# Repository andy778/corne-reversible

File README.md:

# corne-reversible

A wireless Corne-layout split keyboard built on one reversible PCB: the same board is used face-up for the left half and flipped for the right, so a single JLCPCB order of 5 boards covers two keyboards and a spare.

- 3x6+3 (42 keys), with a break-off outer column for 36 keys
- Hot-swap sockets for Kailh MX or Kailh Choc on the same footprint
- Pro Micro-footprint nRF52840 controller (nice!nano v2 or clone), ZMK firmware
- JLCPCB fits the diodes and the reset button (both Basic parts); everything else is hand-soldered
- 3D printed case and plate

Status: planning. Nothing has been fabricated or tested yet.

## Documents

- [Design and build plan](docs/plan.md)
- [Work packages](docs/work-packages.md)

## Layout

| Folder | Contents |
| --- | --- |
| `docs/` | Plan, work packages, build notes |
| `pcb/` | Ergogen config, KiCad project, fabrication outputs |
| `firmware/` | ZMK config and keymap |
| `case/` | Parametric case and plate sources, printable files |

## Licence

Hardware and software in this repository are released under the [MIT Licence](LICENSE). Copyright (c) 2026 andy778.

Third-party footprints and other imported design files keep their own licences. Each one is recorded in `pcb/footprints/THIRD_PARTY.md`.

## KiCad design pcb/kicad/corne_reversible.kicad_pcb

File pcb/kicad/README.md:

# KiCad board (WP7)

Routed KiCad 10 project for one reversible Corne half. LEFT half = KiCad F side up, RIGHT half = the same board flipped (KiCad B up). JLCPCB assembles KiCad B (face A): 21 diodes and the reset button. Fabrication outputs are in [`../fab/`](../fab/README.md).

**Status:** routed, KiCad DRC 0 errors, geometric netlist check passing for both halves. **Not reviewed:** WP8 does the independent pre-order review. Nothing here has been sent to JLCPCB.

## Contents

| Path | What |
| --- | --- |
| `corne_reversible.kicad_pcb` / `.kicad_pro` | The board and its design rules (generated, do not hand-edit without re-running the checks) |
| `fp-lib-table` | Project libraries: `corne_reversible` = `../footprints/corne_reversible.pretty` (WP5), `corne_kicad_local` = `corne_kicad_local.pretty` |
| `corne_kicad_local.pretty/` | The two Ergogen-local footprints (SOD-123 diode on face A, M2 hole), exported in front form so KiCad can check board copies against them |
| `tools/build_board.py` | Builds the routed board from the Ergogen output (see Regenerate) |
| `tools/router.py` | The small grid maze router `build_board.py` uses for the inter-key nets |
| `tools/check_netlist.py` | Electrical check from copper geometry, both halves; output in `netlist-check.txt` |
| `tools/make_fab.py` | Gerbers, drill, JLCPCB BOM/CPL, previews into `../fab/` |
| `tools/kutil.py` | pcbnew helpers |
| `drc-report.txt` | `kicad-cli pcb drc --severity-all` of the committed board |
| `netlist-check.txt` | Output of `check_netlist.py` on the committed board |

## Regenerate

Tools used: Ergogen **4.2.1** (`npx`), KiCad **10.0.6** (`kicad-cli`, and the `pcbnew` Python module of the system Python, `/usr/bin/python3`, 3.14 on the build machine), `shapely` 2.1, `numpy`, `scipy`, `Pillow`. Freerouting was not installed and not used.

```sh
cd pcb/ergogen && npx -y ergogen@4.2.1 . -o output --clean --debug --svg && python3 check.py && cd ../..
/usr/bin/python3 pcb/kicad/tools/build_board.py          # about 5 minutes; deterministic
(cd pcb/kicad && kicad-cli pcb drc --severity-all -o drc-report.txt corne_reversible.kicad_pcb)
/usr/bin/python3 pcb/kicad/tools/check_netlist.py > pcb/kicad/netlist-check.txt
/usr/bin/python3 pcb/kicad/tools/make_fab.py
```

`build_board.py` reads `pcb/ergogen/output/pcbs/corne_reversible.kicad_pcb` (KiCad 5 format from Ergogen), and:

1. assigns the JLCPCB data (value, `LCSC` field) to the diodes (C81598) and the TS-1187A (C318884), and points the two Ergogen-local footprints at `corne_kicad_local`;
2. removes the net from the placeholder battery jumper pads (`BAT+`/`BAT-`) and from the power switch's unused pin 3 (see Power);
3. places a fixed per-key template (identical for all 21 keys, rotated with the key): it joins the four column socket pads, the four anode socket pads and the diode anode, and puts a via on the diode cathode;
4. places the controller fan-out stubs (see Controller) and the nice!view jumper stubs and lanes;
5. routes everything else with `router.py` (0.05 mm grid, two layers, then pulled straight with exact clearance checks), in a fixed order with per-net layer preferences: power and display nets first on the right of the controller, then rows (F preferred) and columns (B preferred) inside the key field, then the long column and row runs into the controller;
6. removes router leftovers (dead-end stubs, single-layer vias) and trims overhangs at T-junctions;
7. moves the controller's jumper instruction text clear of the nice!view labels and adds the version and half labels.

## Board

| | |
| --- | --- |
| Size | **146.28 x 84.01 mm** (outline bounding box, 42-key), 100.9 cm2. 2 layers, 1.6 mm |
| Origin | KiCad (0, 0) = centre of the outer-column bottom key; Ergogen coordinates are the same with y negated |
| Copper | 669 track segments (3.15 m), 106 vias (0.6/0.3 mm) |
| Mounting holes | M2, 2.2 mm NPTH, Ergogen frame: H1 (30.075, 32.65), H2 (65.675, 34.54), H3 (30.075, 13.6), H4 (85.725, -25.645), H5 (115.75, 3.855). H1-H4 moved in this WP for the case inserts (see `pcb/ergogen/README.md`) |
| Break line | x = 9.525 (KiCad), 38 NPTH holes of 0.6 mm (footprint `BRK1`, converted from Ergogen's Edge.Cuts circles by `build_board.py`, WP8 S1) |

## Design rules (JLCPCB 2-layer, from docs/bom.md)

Conservative values where space allows; the absolute JLCPCB minimum is in brackets.

| Rule | Board setting | JLCPCB |
| --- | --- | --- |
| Clearance, copper to copper | 0.20 mm | 0.10 (0.15 recommended) |
| Track width, minimum | 0.20 mm (only the nice!view lanes use 0.20) | 0.10 |
| Signal tracks | 0.25 mm | |
| Power tracks | BAT_P 0.50, RAW 0.50, GND 0.40 (JST, reset, controller), VCC 0.30 mm; 0.30 mm where they pass between the controller hole rows (0.84 mm gaps). nice!view GND 0.25 | |
| Vias | 0.6 mm pad / 0.3 mm drill (ring 0.15) | 0.15 / 0.25 min, 0.2 hole preferred |
| Minimum via annular ring | 0.15 mm (the controller's 0.7/0.3 via-pads have 0.20) | |
| Minimum through hole | 0.30 mm | 0.15 (via), 0.2 preferred |
| Copper to drill hole | 0.25 mm | |
| Hole to hole | 0.50 mm | 0.20 via, 0.45 pad |
| Copper to board edge (incl. mouse-bite holes) | 0.30 mm | 0.20 |
| Text height / thickness | 0.8 / 0.15 mm (footprint silk is 0.9 mm) | 1.0 mm recommended, 0.15 line |

Net classes: Default 0.25, Power (BAT_P, RAW) 0.5, Ground (GND) 0.4, Logic3V3 (VCC) 0.3, all 0.2 mm clearance.

## Routing decisions

**Per key** (template, key frame; B = KiCad B.Cu, F = KiCad F.Cu): column pads 1 are on B on the right of the key and on F on the left; anode pads 2 the other way round. Column: F Choc - F MX, an F track over the top of the key to a via, B to the B Choc pad, B Choc - B MX. Anode: B Choc - B MX down the left side, F Choc - F MX down the right side, both into a via below the MX pads, B to the diode anode. Row: diode cathode on B to a via left of the diode. Column trunks run vertically on B, rows horizontally on F, so the key field is close to a Manhattan grid.

**Matrix to controller.** The long column runs (the outer columns in particular) go along the top edge of the key field or through the gaps between key rows, then down the strip left of the controller; rows enter the same strip from the key field and the thumb cluster. The router chose these paths; see the previews. Thumb keys connect to their column nets (near = D18 under the index column, mid = D15, far = D14).

**Controller** (`MCU1`, socketed, face-up on both halves). The board net goes to the centre via-pad of each pin exactly as `pcb/footprints/README.md` describes; the jumpers select the half. Each used via-pad is reached by a hand-placed stub through the gap between two hole rows (0.84 mm between hole pads), on the face and side where the via-pad has no link of another net. Left side: columns on F (D21 ... D14), rows on B (D4 ... D7). Right side: RAW, GND, RST, VCC on B; D1 (CS), D2 (MOSI), D3 (SCK) on F. The three controller GND via-pads are tied inside the footprint: the adjacent pair of rows 2/3 with a short B track, rows 3/4 through their two F-side GND jumper pads (both are GND-side pads, so this is plain GND copper on both halves). Nothing else is routed between the hole columns.

**nice!view.** Each jumper target pad gets a stub out of its mask aperture, away from the jumper gap. F pads dog-leg to a via 0.9 mm to their left; B pads go straight down. Under the header four nested lanes per face (0.20 mm) run to the right, where the router joins them to the controller. CS = D1, MOSI = D2, SCK = D3, plus VCC and GND, both halves (checked).

**Power.** JST pin 2 (BAT_P, both hole pairs) -> MSK12C02 pin 1 (both faces) ; MSK12C02 common pin 2 (both faces) -> controller RAW. JST pin 1 and the reset button go to GND. Decision on the WP5 battery placeholder holes `HB1`/`HB2` (B+/B-): **kept, but their jumper target pads have no net and nothing is routed to them.** The plan asked for the holes, and on a socketed nice!nano or SuperMini the battery reaches the controller through RAW. With no copper on the target pads, bridging a B+/B- jumper on either or both faces connects the hole to an isolated pad, so the CRITICAL battery short in the WP5 hazard table cannot happen on this board. If a future controller needs B+ there, that is a board change.

**Mounting holes.** The router keeps its copper at least 2.6 mm (copper edge) from every mounting-hole centre, outside an M2 screw head (3.8 mm). Measured nearest copper edge from the centre: H1 2.60, H2 2.35, H3 2.60, H4 2.61, H5 1.50 mm. H5's 1.50 mm is the nice!view MOSI lane on F (and the CS lane on B, under the plastic boss); a single net under the screw head cannot short to anything even if the mask is scratched, but a nylon washer at H5 costs nothing.

**Reset.** TS-1187A pin 1 (both pads) -> RST, pin 2 (both pads) -> GND.

**Break-off tab.** Only COL_D21, ROW0, ROW1 and ROW2 cross x = 9.525 (checked); they cross in the three gaps of the perforation, at least 0.30 mm from every bite hole. No other copper is in the tab. With the tab removed the remaining 18 keys and everything else stay connected (checked).

**No ground pour.** GND only has to connect the JST, the reset button, three controller via-pads and the display, all within 30 mm of each other on the right of the controller; tracks do that. A pour on both faces would sit against the hand-bridged jumper pads (a solder blob could reach it), wick heat from the socket pads, need a keep-out along the break line, and put copper under the controller module's antenna end. So none.

**Silkscreen.** From WP5: `LEFT HALF: BRIDGE 24 PIN / JUMPERS ON THIS FACE ONLY / USB / CONTROLLER FACE UP` on F and the `RIGHT HALF` version on B (moved below the nice!view header so it no longer overlaps the display pin labels), pin names at every controller hole and nice!view hole on both faces, `LEFT: bridge 4` / `RIGHT: bridge 4` at the display, B+/B- marked. Added: `corne-reversible v1.0 2026-11-15` on both faces and `LEFT HALF: THIS FACE UP` (F) / `RIGHT HALF: THIS FACE UP` (B). Polarity: every diode has a cathode bar on B silk at the cathode pad; the JST has `+`/`-` and `USE THIS PAIR` on F; on B (next to the controller pin labels) only `+`/`-`, set beside the B pair in the gaps between the labels; the F pair has no B silk, so the marked pair is the one to use (WP8 S2).

## DRC result

`drc-report.txt`, KiCad 10.0.6, all severities: **0 errors, 0 unconnected items, 69 warnings**, none excluded. Accepted warnings:

| Count | Type | Why accepted |
| --- | --- | --- |
| 42 | `hole_to_hole` | The two overlapping 3.0 mm MX socket holes per key (2 per key), inherent to the reversible MX footprint (WP5). The fab drills a figure-8; JLCPCB's DFM may ask, answer "intended". Left as warnings rather than DRC exclusions so they stay visible on every run |
| 16 | `npth_inside_courtyard` | The break-line NPTH holes (`BRK1`) sit on the key-tile boundary, inside the socket courtyards; copper is at least 0.30 mm away. The same holes were outline circles before WP8 S1 and drew no finding then |
| 8 | `silk_over_copper` | Controller pin labels next to the JST/reset pads; JLCPCB clips silk on pads. Legibility of a few right-half pin labels (B face, D2-D8) is reduced; the pin map is printed on the F face and in the WP5 README |
| 2 | `silk_overlap` | The same labels touching the reset and JST outlines |
| 1 | `lib_footprint_mismatch` | `SW22` (TS-1187A): value and the `LCSC` field were set on the board copy |

All other footprints match their library copies, which also confirms that the Ergogen modules and the WP5 `.kicad_mod` files are the same footprints.

## Netlist check

`tools/check_netlist.py` builds connectivity from the copper itself (pads, tracks, vias, plated holes), bridges the jumpers of one face (LEFT: F, RIGHT: B), maps each controller hole to the Pro Micro pin that lands in it on that half (mirrored on the right half) and asserts per key: column pin -> all four pad-1 socket pads, pad 2 -> diode anode, diode cathode -> row pin, for both halves against the stock ZMK Corne pin map; power, reset and nice!view wiring; no two controller pins sharing copper; unused pins isolated; the 36-key break; the break-line crossings; that bridging both faces does short pins (the documented hazard); and that every copper island carries one net name. Result on the committed board: `netlist-check.txt`, **271 checks, ALL PASS**.

## Known limits

- The router is mine and simple; routes are valid (DRC) but not pretty in places, notably around the nice!view and on the right of the controller. Open the board in KiCad before ordering.
- The right edge layout (power switch, reset, JST next to the controller) is WP4's and is tight; see the silk warnings above.
- Everything listed under "Unverified" in `pcb/footprints/README.md` and `pcb/ergogen/README.md` still applies.

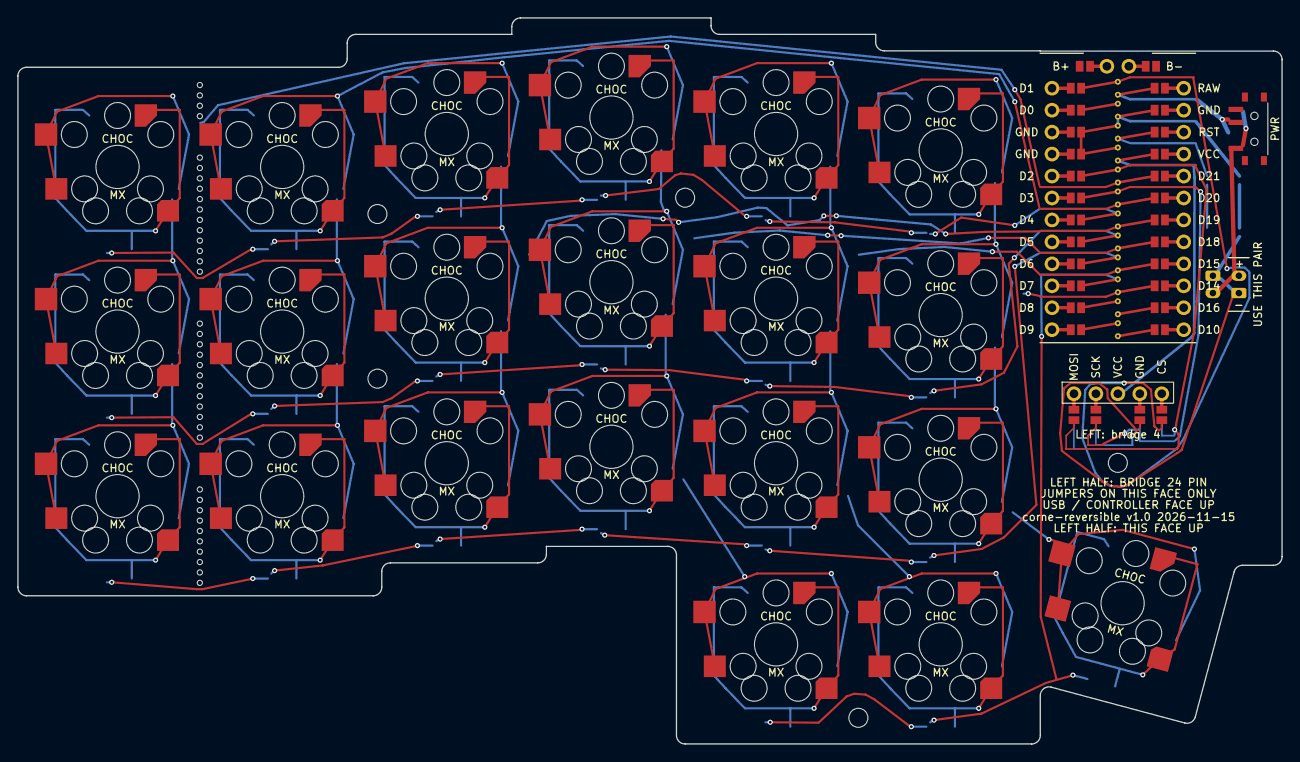
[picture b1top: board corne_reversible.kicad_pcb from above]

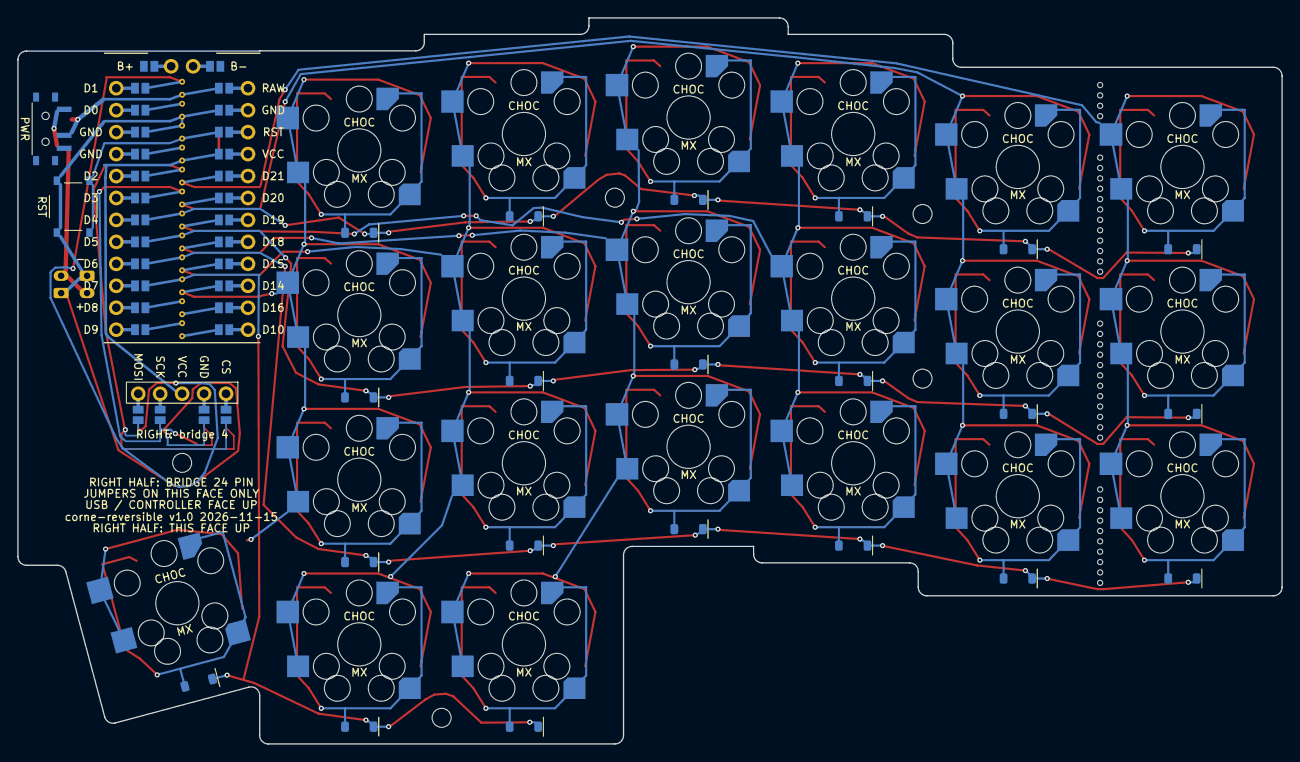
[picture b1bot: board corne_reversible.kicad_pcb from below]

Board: 2 copper layers, 146.3 x 84.0 mm, 53 parts (22 on the bottom side), 39 nets.

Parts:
BRK1: BreakLine_Perforation_NPTH
BT1: JST_PH_S2B-PH-K_Reversible
D1, D2, D3, D4, D5, D6, D7, D8, D9, D10, D11, D12, D13, D14, D15, D16, D17, D18, D19, D20, D21: 1N4148W; D_SOD-123_Back
DISP1: Display_niceview_Header_Reversible_Jumpers
H1, H2, H3, H4, H5: MountingHole_2.2mm_M2
MCU1: MCU_ProMicro_nRF52840_Reversible_Jumpers
PWR1: SW_SPDT_MSK12C02_Reversible
SW1, SW2, SW3, SW4, SW5, SW6, SW7, SW8, SW9, SW10, SW11, SW12, SW13, SW14, SW15, SW16, SW17, SW18, SW19, SW20, SW21: SW_MX_Choc_Hotswap_Reversible
SW22: TS-1187A-B-A-B; SW_Reset_TS-1187A_FaceA

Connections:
BAT_P: BT1.2, PWR1.1
COL_D14: MCU1.D14, SW16.1, SW17.1, SW18.1, SW21.1
COL_D15: MCU1.D15, SW13.1, SW14.1, SW15.1, SW20.1
COL_D18: MCU1.D18, SW10.1, SW11.1, SW12.1, SW19.1
COL_D19: MCU1.D19, SW7.1, SW8.1, SW9.1
COL_D20: MCU1.D20, SW4.1, SW5.1, SW6.1
COL_D21: MCU1.D21, SW1.1, SW2.1, SW3.1
DISP_CS: DISP1.CS, MCU1.D1
DISP_MOSI: DISP1.MOSI, MCU1.D2
DISP_SCK: DISP1.SCK, MCU1.D3
GND: BT1.1, DISP1.GND, MCU1.GND, SW22.2
RAW: MCU1.RAW, PWR1.2
ROW0: D3.1, D6.1, D9.1, D12.1, D15.1, D18.1, MCU1.D4
ROW1: D2.1, D5.1, D8.1, D11.1, D14.1, D17.1, MCU1.D5
ROW2: D1.1, D4.1, D7.1, D10.1, D13.1, D16.1, MCU1.D6
ROW3: D19.1, D20.1, D21.1, MCU1.D7
RST: MCU1.RST, SW22.1
SW_far_thumb: D21.2, SW21.2
SW_index_bottom: D13.2, SW13.2
SW_index_home: D14.2, SW14.2
SW_index_top: D15.2, SW15.2
SW_inner_bottom: D16.2, SW16.2
SW_inner_home: D17.2, SW17.2
SW_inner_top: D18.2, SW18.2
SW_mid_thumb: D20.2, SW20.2
SW_middle_bottom: D10.2, SW10.2
SW_middle_home: D11.2, SW11.2
SW_middle_top: D12.2, SW12.2
SW_near_thumb: D19.2, SW19.2
SW_outer_bottom: D1.2, SW1.2
SW_outer_home: D2.2, SW2.2
SW_outer_top: D3.2, SW3.2
SW_pinky_bottom: D4.2, SW4.2
SW_pinky_home: D5.2, SW5.2
SW_pinky_top: D6.2, SW6.2
SW_ring_bottom: D7.2, SW7.2
SW_ring_home: D8.2, SW8.2
SW_ring_top: D9.2, SW9.2
VCC: DISP1.VCC, MCU1.VCC

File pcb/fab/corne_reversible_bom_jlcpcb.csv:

Comment,Designator,Footprint,LCSC Part #
1N4148W,"D1,D2,D3,D4,D5,D6,D7,D8,D9,D10,D11,D12,D13,D14,D15,D16,D17,D18,D19,D20,D21",D_SOD-123_Back,C81598
TS-1187A-B-A-B,SW22,SW_Reset_TS-1187A_FaceA,C318884

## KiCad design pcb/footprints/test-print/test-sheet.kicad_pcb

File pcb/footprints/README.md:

# Footprints (WP5)

Reversible footprints for the corne-reversible board, in KiCad and Ergogen form, plus the checks and the 1:1 paper test sheet.

**Status:** generated, KiCad DRC-checked and geometry-checked. **Paper-tested:** the WP5 acceptance check, a 1:1 test fit with real parts (see [Paper test](#paper-test)), passed on 2026-11-15.

## Contents

| Path | What |
| --- | --- |
| `corne_reversible.pretty/` | KiCad 8/9/10 footprint library (file format 20240108, opens in KiCad 8 and later) |
| `ergogen/` | Ergogen v4 footprint modules with the same geometry. Copy or symlink into `<ergogen project>/footprints/corne/` and use `what: corne/<file name>` |
| `tools/gen_footprints.py` | **Source of truth.** Generates both of the above. Edit this, never the outputs |
| `tools/check_footprints.py` | Geometry and clearance checker against JLCPCB 2-layer rules (needs `shapely`) |
| `tools/make_test_sheet.py` | Builds `test-print/test-sheet.kicad_pcb` and plots the PDF; also runs KiCad DRC |
| `test-print/test-sheet.pdf` | 1:1 printable sheet. Page 1 shows the KiCad F side; page 2 shows the KiCad B side seen from B |
| `test-print/drc-report.txt` | KiCad 10 DRC of the test board against JLCPCB rules |
| `THIRD_PARTY.md` | Sources, commits and licences |

Regenerate everything:

```sh
python3 pcb/footprints/tools/gen_footprints.py
python3 pcb/footprints/tools/check_footprints.py
python3 pcb/footprints/tools/make_test_sheet.py --pdf --drc
```

## Face convention (read this first)

The plan calls the faces A and B: face A is the underside of the left half and the top of the right half. Diodes go on face A.

The footprints assume this mapping:

| | LEFT half | RIGHT half |
| --- | --- | --- |
| Board orientation | KiCad **F** side up | flipped left to right, KiCad **B** side up |
| Face A (JLCPCB diodes) | underside = KiCad **B** | top = KiCad **B** |
| Sockets, power switch, reset, JST | soldered on KiCad B | soldered on KiCad F |
| Controller and nice!view | on top (KiCad F), component side up | on top (KiCad B), component side up |
| Jumpers to bridge | the ones on **KiCad F** (silk: `LEFT HALF: BRIDGE 24 PIN JUMPERS ON THIS FACE ONLY`) | the ones on **KiCad B** (silk: `RIGHT HALF: …`) |

So **WP7 places the diodes on KiCad B.Cu**, and JLCPCB assembles the bottom side. To use the opposite mapping, set `LEFT_FACE = "B"` in `gen_footprints.py` and regenerate. Every LEFT/RIGHT label and jumper net then swaps sides.

The flip is a left-right mirror: a point at KiCad (x, y) is seen at (-x, y) from the top of the right half. The USB end stays at -y on both halves.

## Footprints

All footprints are marked `exclude_from_pos_files exclude_from_bom` because only the diodes are factory-placed. WP7 can change that if a full BOM is wanted. **No hand-soldered pad has paste.** This matters most for the jumpers: paste on face-A jumpers would let JLCPCB's stencil bridge all of them. Do not add paste.

### `SW_MX_Choc_Hotswap_Reversible` / `ergogen/switch_mx_choc_reversible.js`

One key, 19.05 mm pitch. Origin is the key centre.

- **MX** (Kailh CPG151101S11) pads and holes are on the +y half. The MX switch is rotated 180 degrees (south-facing), which is what makes room for Choc. The socket pads are on both faces. The inner pad is chamfered to clear the other face's socket hole.
- **Choc** (Kailh CPG135001S30) pads and holes are on the -y half, on both faces, sharing the pin-1 hole at (0, -5.95). The inner pad is chamfered (50 %) to clear the other face's side hole.
- Centre hole is 5.0 mm, for the Choc V2 post. Each side peg uses one oval slot, 2.32 x 1.9 mm centred at ±5.29, which takes both the MX PCB-mount pegs (±5.08) and the Choc V1 pegs (±5.5).
- Pads: `1` = column side (`from`), `2` = diode side (`to`). Each net appears on 4 pads: MX F, MX B, Choc F, Choc B. The faces are **not joined inside the footprint**, so WP7 routes both. A switch is a plain contact, so the pad-to-net choice per socket is free; it was picked so pad 1 is at the outer x edge (column traces run vertically) and pad 2 is nearest the diode below for MX.
- Fab and courtyard layers: approximate socket outlines on both faces. Dwgs.User: 14 x 14 mm switch outline and 18.05 mm keycap outline.

### `MCU_ProMicro_nRF52840_Reversible_Jumpers` / `ergogen/mcu_promicro_reversible_jumpers.js`

Pro Micro footprint for the nice!nano v2 or a SuperMini. It is socketed and mounted **component side up on both halves**, with USB towards -y. The rows are 15.24 mm apart; holes are 1.0 mm drill with 1.7 mm pads, for machine-pin sockets.

- **Holes `H1`..`H24`** use Pro Micro numbering in the LEFT-half view: H1 is top-left (D1) and the numbering runs counter-clockwise. Each hole is a local net with nothing attached except its two jumpers.
- **Per hole, one jumper on each face** (0.9 x 1.25 mm pads, 0.3 mm gap, one shared mask opening, tented copper link to the hole):
  - KiCad F jumper: connects the hole to the pin the LEFT half seats there.
  - KiCad B jumper: connects the hole to the pin the RIGHT half seats there, which is the pin at the mirrored hole.
- **Signal pads** are named after the controller pin: `D0`..`D21`, `RAW`, `GND`, `RST`, `VCC`. Each signal has a 0.7 / 0.3 mm tented via-pad in the centre column (x = 0, y = row ± 0.75). Its F jumper and its mirrored B jumper are already tied to it inside the footprint. **WP7 routes the board net to that via.** In Ergogen, pass the board net as the param, e.g. `D4: ROW0`.
- **`BAT+` / `BAT-` (holes `HB1`, `HB2`)** sit next to the USB end at y = -15.24, x = ±1.27, with jumpers as for the other pins. They are a **placeholder**: see the unverified list. With a nice!nano v2 the normal battery path is JST, then power switch, then the `RAW` pin. Leave these unbridged and unrouted unless your controller really has B+/B- holes at exactly these positions.
- Silk on each face gives the pin name at every hole as seen on that half, plus the bridging instruction.
- The nice!nano extra pins (P1.01, P1.02, P1.07) are **not** included. They sit in different places on the nice!nano and the SuperMini, and the Corne does not need them.

### `Display_niceview_Header_Reversible_Jumpers` / `ergogen/display_niceview_reversible_jumpers.js`

A 5-pin 2.54 mm header. Seen from the top of the LEFT half, x = -5.08 to +5.08: **MOSI, SCK, VCC, GND, CS**. VCC is the centre pin and mirrors onto itself, so it is a plain pad `VCC`. The other four holes (`H1`, `H2`, `H4`, `H5`) each have one jumper per face, placed below the header:

| Hole (left view) | KiCad F jumper (LEFT) | KiCad B jumper (RIGHT) |
| --- | --- | --- |
| H1 (x = -5.08) | MOSI | CS |
| H2 (x = -2.54) | SCK | GND |
| H3 (x = 0) | VCC (no jumper) | VCC |
| H4 (x = +2.54) | GND | SCK |
| H5 (x = +5.08) | CS | MOSI |

The jumper target pads are named `MOSI`, `SCK`, `GND`, `CS`. They are **not** joined inside the footprint, because the F and B copies cross each other. WP7 routes them: MOSI to D2, SCK to D3, CS to D1, plus GND and VCC.

### Edge parts (soldered by hand on whichever face is the underside)

These parts carry their own pads on each face, mirrored, with the same pad numbers. So the pin function is right on both faces **without jumpers**. The F and B copies are separate copper that WP7 joins.

| Footprint | Part (WP3, LCSC, checked 2026-11-15) | Pads / nets | Notes |
| --- | --- | --- | --- |
| `SW_SPDT_MSK12C02_Reversible` | Shou Han MSK12C02, C431540 | `1` = BAT_P (from JST), `2` = common, goes to RAW, `3` = NC; 4 unnamed shell tabs; 2 NPTH | Actuator towards +y (board edge). Signal pads lengthened 0.4 mm away from the body for hand soldering. Because the B copy is mirrored, ON is the opposite slide direction on the two halves. |
| `SW_Reset_TS-1186F_Side_Reversible` | XKB TS-1186F-B-A, C908470. **Fallback only**: the owner chose the factory-fitted TS-1187A (below) | `1` = RST (pins 1+2), `2` = GND (pins 3+4); two 0.8 mm peg holes | Land pattern read from the XKB TS-1186F-X-X drawing; pads lengthened 0.4 mm outward. Actuator assumed towards +y. |
| `JST_PH_S2B-PH-K_Reversible` | JST S2B-PH-K-S, C173752, THT side entry | `1` = BAT_N (GND), `2` = BAT_P | THT holes are shared by both faces, so a connector fitted on the other face would swap polarity. This footprint therefore has **two hole pairs**: y = 0 for a connector on KiCad F, y = -3.0 for one on KiCad B, wired as mirror images. No jumpers, so there is no double-bridge battery short. Silk on each face marks `USE THIS PAIR`. Courtyard includes the plug and lead. |

### `SW_Reset_TS-1187A_FaceA` / `ergogen/reset_switch_ts1187a_face_a.js` (JLCPCB-assembled)

- XKB TS-1187A-B-A-B, C318884, **JLCPCB Basic** (no feeder fee): the owner chose to have JLCPCB fit it with the diodes, on face A only.
- Pads, paste and courtyard are KiCad's stock `SW_Push_1P1T_XKB_TS-1187A` (1.0 x 0.75 mm at x +-3.0, y +-1.875). `1` = RST, `2` = GND. Included in BOM and position files, unlike the hand-soldered footprints.
- The KiCad library copy is front-side; flip it onto face A in KiCad. The Ergogen module is emitted already on face A (KiCad B with the default `LEFT_FACE`).
- It is top-actuated, 1.5 mm tall. Left half: it faces down, so the tray needs a press hole under it. Right half: it faces up, so place it outside the switch plate (next to the controller), not under a key.

## Corne pin map (ZMK stock `corne` shield)

Source: zmkfirmware/zmk `main` at `4de313367288aad5aeaa1243890e40dc813f7008`:
[`corne.dtsi`](https://github.com/zmkfirmware/zmk/blob/4de313367288aad5aeaa1243890e40dc813f7008/app/boards/shields/corne/corne.dtsi),
[`corne_left.overlay`](https://github.com/zmkfirmware/zmk/blob/4de313367288aad5aeaa1243890e40dc813f7008/app/boards/shields/corne/corne_left.overlay),
[`corne_right.overlay`](https://github.com/zmkfirmware/zmk/blob/4de313367288aad5aeaa1243890e40dc813f7008/app/boards/shields/corne/corne_right.overlay).
GPIO names are from [`nice_nano/arduino_pro_micro_pins.dtsi`](https://github.com/zmkfirmware/zmk/blob/4de313367288aad5aeaa1243890e40dc813f7008/app/module/boards/nicekeyboards/nice_nano/arduino_pro_micro_pins.dtsi).

**Diode direction: `col2row`.** Current flows from the column, through the switch, into the diode anode and out of the cathode to the row. So: column net goes to switch pad `1`, switch pad `2` goes to the diode **anode**, and the diode **cathode** (band) goes to the row net. Rows are inputs with pull-down.

| Matrix line | Pro Micro pin (`&pro_micro N`) | nRF52840 GPIO | Physical position |
| --- | --- | --- | --- |
| Row 0 | D4 | P0.22 | top row |
| Row 1 | D5 | P0.24 | home row |
| Row 2 | D6 | P1.00 | bottom row |
| Row 3 | D7 | P0.11 | thumb row (3 keys, under columns 3 to 5) |
| Column, outer pinky | D21 | P0.31 | left `col-gpios[0]`, right `col-gpios[5]` |
| Column, pinky | D20 | P0.29 | left [1], right [4] |
| Column, ring | D19 | P0.02 | left [2], right [3] |
| Column, middle (and outer thumb) | D18 | P1.15 | left [3], right [2] |
| Column, index (and middle thumb) | D15 | P1.13 | left [4], right [1] |
| Column, inner index (and inner thumb) | D14 | P1.11 | left [5], right [0] |

Left `col-gpios` = 21, 20, 19, 18, 15, 14 (outer to inner). Right `col-gpios` = 14, 15, 18, 19, 20, 21 (inner to outer), with `col-offset = <6>`. **The same physical column uses the same pin on both halves**: the outer pinky column is D21 on both, the inner index column is D14 on both. A flipped board gives exactly this, so the board nets are simply `ROW0..3` and `COL_D21 … COL_D14` on one copper layout. The 36-key break-off tab carries the D21 column. The 5-column ZMK transform drops RC(x,0) and RC(x,11).

Not used by the Corne matrix: D0, D1, D2, D3, D8, D9, D10, D16. D1, D2 and D3 go to the nice!view.

## nice!view mapping (stock `nice_view_adapter`)

Source: [`nice_view_adapter/boards/nice_nano_nrf52840_zmk.overlay`](https://github.com/zmkfirmware/zmk/blob/4de313367288aad5aeaa1243890e40dc813f7008/app/boards/shields/nice_view_adapter/boards/nice_nano_nrf52840_zmk.overlay) and [`README.md`](https://github.com/zmkfirmware/zmk/blob/4de313367288aad5aeaa1243890e40dc813f7008/app/boards/shields/nice_view_adapter/README.md) at the same commit. Confirmed by [nicekeyboards docs](https://nicekeyboards.com/docs/nice-view/pinout-schematic) and WP3.

| nice!view pin | Pro Micro pin | nRF52840 | ZMK |
| --- | --- | --- | --- |
| MOSI | D2 | P0.17 | `SPIM_MOSI` (same pin as the Corne OLED SDA) |
| SCK | D3 | P0.20 | `SPIM_SCK` (same pin as the Corne OLED SCL) |
| CS | D1 | P0.06 | `cs-gpios = <&pro_micro 1 …>` |
| VCC | VCC (3.3 V) | | |
| GND | GND | | |

The adapter also assigns MISO to P0.25, which is not a Pro Micro pin and is not connected. The adapter disables `pro_micro_i2c`. With this wiring, `corne_left nice_view_adapter nice_view` builds unmodified.

## Jumper scheme and per-pin hazards

On each half, bridge **only** the jumpers on the face pointing up: KiCad F on the left half, KiCad B on the right. Bridging a hole on both faces shorts the two nets in the table below. Bridging the **wrong** face on a half mirrors the whole pinout, which puts battery voltage on a GPIO and shorts VCC to GND, so it is **destructive**. The hazard is the same for the hole at -x and its mirror at +x.

| Row (from USB end) | Left-half pin at -x | Left-half pin at +x | If both faces are bridged | Severity |
| --- | --- | --- | --- | --- |
| 1 | D1 (nice!view CS) | RAW (battery, up to 4.2 V) | Battery on P0.06, above the nRF52840's VDD + 0.3 V limit. Can destroy the GPIO or MCU and the display input | **HIGH** |
| 2 | D0 (unused) | GND | D0 grounded | low |
| 3 | GND | RST | Held in reset, never boots | low (no damage) |
| 4 | GND | VCC (3.3 V out) | 3.3 V rail shorted: regulator overload and heat, battery drain, display dead | **HIGH** |
| 5 | D2 (MOSI) | D21 (col, outer pinky) | Display data on a column: garbage on the display, ghost keys | medium |
| 6 | D3 (SCK) | D20 (col) | as above | medium |
| 7 | D4 (row 0) | D19 (col) | Driven column into a row input: whole-row ghosting | medium (no damage) |
| 8 | D5 (row 1) | D18 (col) | as above | medium |
| 9 | D6 (row 2) | D15 (col) | as above | medium |
| 10 | D7 (row 3) | D14 (col) | as above | medium |
| 11 | D8 (unused) | D16 (unused) | none | none |
| 12 | D9 (unused) | D10 (unused) | none | none |
| USB end | BAT+ | BAT- | **Direct battery short, no fuse.** Placeholder holes: leave unbridged | **CRITICAL** |
| nice!view H1/H5 | MOSI (D2) | CS (D1) | Display garbage | low |
| nice!view H2/H4 | SCK (D3) | GND | SPI clock pin driven into ground | low to medium |

GND has to be jumpered too. The three controller GND pins are at left-view rows 2 (+x), 3 (-x) and 4 (-x); they mirror onto D0, RST and VCC, so no pin is symmetric and all 24 holes need jumpers.

**Before fitting the controller or connecting the battery**, with a multimeter:

1. RAW net to GND net: open circuit.
2. VCC net to GND net: open circuit.
3. For each bridged hole, continuity from the hole to the net named on the silk at that hole on the upward face.
4. No jumper bridged on the downward face (check visually before the case goes on).

## Diode clearance (face A, between vertically adjacent keys)

Checked with KiCad's stock `D_SOD-123` (pads 0.9 x 1.2 mm at ±1.65 mm, courtyard 4.7 x 2.3 mm). The diode is placed on KiCad B, centred between two keys (y = +9.525 from the upper key), long axis across the column.

| Check | Result |
| --- | --- |
| Diode pads to switch copper, key above / key below | 3.58 mm / 1.68 mm |
| Diode pads to nearest NPTH | 1.71 mm (Choc pin-1 hole of the key below) |
| Diode courtyard to socket courtyards, key above (MX) / key below (Choc) | 1.63 mm / **0.03 mm**, tight but not overlapping (the Choc socket outline is approximate) |
| Top side (right half), gap between MX housings at the 15.6 mm bottom flange | 3.45 mm, leaving 0.83 mm each side of a 1.8 mm diode body |
| Top side, gap between Choc V1 housings (15.0 mm) | 4.05 mm, leaving 1.13 mm each side |

This confirms the plan's 3.4 mm (MX) and 4 mm (Choc) budget. A Choc build with diodes on the top face still needs the plate pockets described in the plan.

## Validation results

**KiCad** (`kicad-cli` 10.0.6):

- All six footprints load and plot (`kicad-cli fp export svg`).
- DRC was run on `test-print/test-sheet.kicad_pcb` (4 keys, 2 diodes, every other footprint), with JLCPCB rules in `test-sheet.kicad_pcb`'s project: 0.127 mm clearance, 0.3 mm drill, 0.15 mm via ring, 0.2 mm hole clearance, 0.5 mm hole-to-hole.
- Result: **no clearance, short, annular-ring or silkscreen violations.** The only findings are 8 × `hole_to_hole`, which are the overlapping MX socket holes described below (2 per key), plus "unconnected items" (expected, because the test board is not routed).
- The Ergogen modules were run through Ergogen 4.2.1 on a small test config, with rotated keys and footprints. The output board loads in KiCad. Its DRC shows only the same MX hole overlap, edge clearance against the one-key toy outline, unconnected items and the library-not-configured notice. Ergogen's 0.8 mm minimum text height passes, because all silk text is at least 0.9 mm.

**`tools/check_footprints.py`** (rules: 0.127 mm copper, 0.2 mm hole to copper, 0.5 mm hole to hole, 0.3 mm drill, 0.15 mm ring):

| Footprint | Min copper gap | Min hole to copper | Min hole to hole | Min ring | Violations |
| --- | --- | --- | --- | --- | --- |
| Switch | 8.95 mm (same face, different net) | 0.301 mm (MX inner pad chamfer vs other face's MX hole) | **-0.16 mm** (overlap) | n/a (NPTH) | 4 hole-to-hole, see below |
| Switch, MX pads vs Choc pads, same face | 3.74 mm | MX 0.301 / Choc 0.356 mm to any hole | | | none |
| Controller | 0.30 mm (jumper gap) | 0.54 mm | 0.74 mm | 0.20 mm (via-pads) | none |
| nice!view | 0.30 mm (jumper gap) | 1.19 mm | 1.54 mm | 0.35 mm | none |
| MSK12C02 | 0.60 mm | 0.95 mm | 2.15 mm | | none |
| TS-1186F | 1.20 mm | 1.00 mm | 1.00 mm | | none |
| JST PH THT | 0.80 mm | 1.03 mm | 1.25 mm | 0.225 mm | none |

The 4 switch violations are known and accepted:

- **MX socket holes overlap by 0.16 mm** (3.0 mm drills 2.84 mm apart, at (±3.81, 2.54) and (∓2.54, 5.08)). This is inherent to every reversible MX hot-swap footprint: ceoloide `switch_mx` reversible and the mass-produced Lily58 Pro have the same overlap. The fab drills a figure-8 hole. JLCPCB's DFM check may query it; answer "intended".
- **Peg slot to MX hole web is 0.39 mm** (< 0.5 mm). ceoloide `switch_mx` has the same 0.39 mm. These are NPTH in FR4 with no copper, so the only risk is a fragile web.

## Paper test

`test-print/test-sheet.pdf`, A4 landscape, 2 pages, black and white:

- Page 1: KiCad F side seen from F, which is the top of the LEFT half and the underside of the RIGHT half.
- Page 2: KiCad B side seen from B (plotted mirrored), which is the underside of the LEFT half and the top of the RIGHT half (face A, with the SOD-123 diodes).
- Each page has a 2 x 2 block of keys at 19.05 mm pitch, the controller, the nice!view header, power switch, reset and JST, and a 50 mm horizontal and 50 mm vertical scale bar.

Print at **100 % / actual size**, no fit-to-page. Measure both 50 mm bars before trusting anything else. Then on **both pages**:

1. Lay a Kailh MX socket on the MX pads and a Kailh Choc socket on the Choc pads of each key. The socket bosses should sit on the hole circles and the solder tabs on the pads.
2. Push an MX switch (pins through the paper at the MX holes, rotated so its pins sit in the +y half, i.e. LED window facing away from the Choc pads) and a Choc V1 and a Choc V2 switch. Check the centre posts and pegs line up with the holes and slots. **Check whether your Choc V2 has a corner leg**; there is no hole for it (see below).
3. Check that a socket on one key does not cover the diode on page 2, and that switch housings clear the diode position on the top face of the right half.
4. Push the controller with its sockets or pins through the 24 holes, component side up and USB towards the top of the page. Check every hole lines up and that the pin labels on the silk match the pins printed on your controller, on both pages.
5. Lay the nice!view on its header holes and check the pin order (MOSI, SCK, VCC, GND, CS from left on page 1).
6. Check the MSK12C02, TS-1186F and JST footprints against the parts.

## Unverified / needs physical check

1. **Whole switch footprint**: socket fit on both faces for both socket types. This is the WP5 acceptance test and the main project risk.
2. **Choc V2 corner leg.** Some Choc V2 parts have a leg at (∓5.0, +5.15) mm. That spot is under the MX socket's inner pad on the same face, so there is **no hole** for it. A V2 switch with that leg may not sit flat until the leg is clipped. Check with the real switch.
3. **MX switch location.** The 5.0 mm centre hole (for the Choc V2 post) is 1 mm larger than the MX post, and the peg slots allow about 0.4 mm of x play. MX alignment therefore relies on the plate and the socket. Check that the paper fit feels right.
4. **Socket outlines** on Fab and courtyard layers are approximate bounding boxes, not datasheet drawings. The Choc-to-diode courtyard gap is 0.03 mm.
5. **nice!view header order and orientation**: MOSI, SCK, VCC, GND, CS from the left, seen from the top of the left half. This comes from ceoloide's footprint (reference only); the nicekeyboards pinout is an image. The footprint is symmetric, but if the real order is reversed, the LEFT/RIGHT jumper labels would be wrong. Check against the real display before fab.
6. **Battery holes B+/B-**: position (x = ±1.27, y = -15.24) and whether they are needed at all. The plan asked for them. The nice!nano docs say the battery pads are on the top of the module, which a socket cannot reach, and that RAW/B+ is the battery pin. Confirm on the bought controllers. Otherwise leave them unrouted and unbridged, or delete them.
7. **SuperMini pinout.** It is assumed identical to the nice!nano on the 24 Pro Micro pins (ZMK builds it as `nice_nano`), including RAW = battery+. Measure the bought boards (plan risk list).
8. **Socket hole size.** The 1.0 mm drill for machine-pin sockets, and whether low-profile socket strips (about 2.5 mm wide) clear the inner jumper pads by the assumed 0.45 mm.
9. **Jumper size.** The 0.9 x 1.25 mm pads with a 0.3 mm gap: confirm they are easy to bridge with an iron and easy to clear again.
10. **MSK12C02**: that pin 2 is the common, the actuator side, and that the lengthened pads still suit the part.
11. **TS-1186F-B-A is provisional.** The land pattern was read by eye from the scanned XKB drawing. The pin 1+2 / 3+4 pairing comes from its circuit diagram. The actuator direction relative to the pads is assumed.
12. **JST two-pair layout.** A connector pushed into the other face's pair has reversed polarity; follow the `USE THIS PAIR` silk. **Battery lead polarity varies by vendor**: check it against the `+`/`-` silk before plugging in.
13. **JLCPCB rule values** are assumed (0.2 mm hole to copper, 0.5 mm hole to hole). Confirm on jlcpcb.com on the day of ordering.
14. **Face convention** (LEFT = KiCad F up, diodes on KiCad B) must match what WP4 and WP7 do.

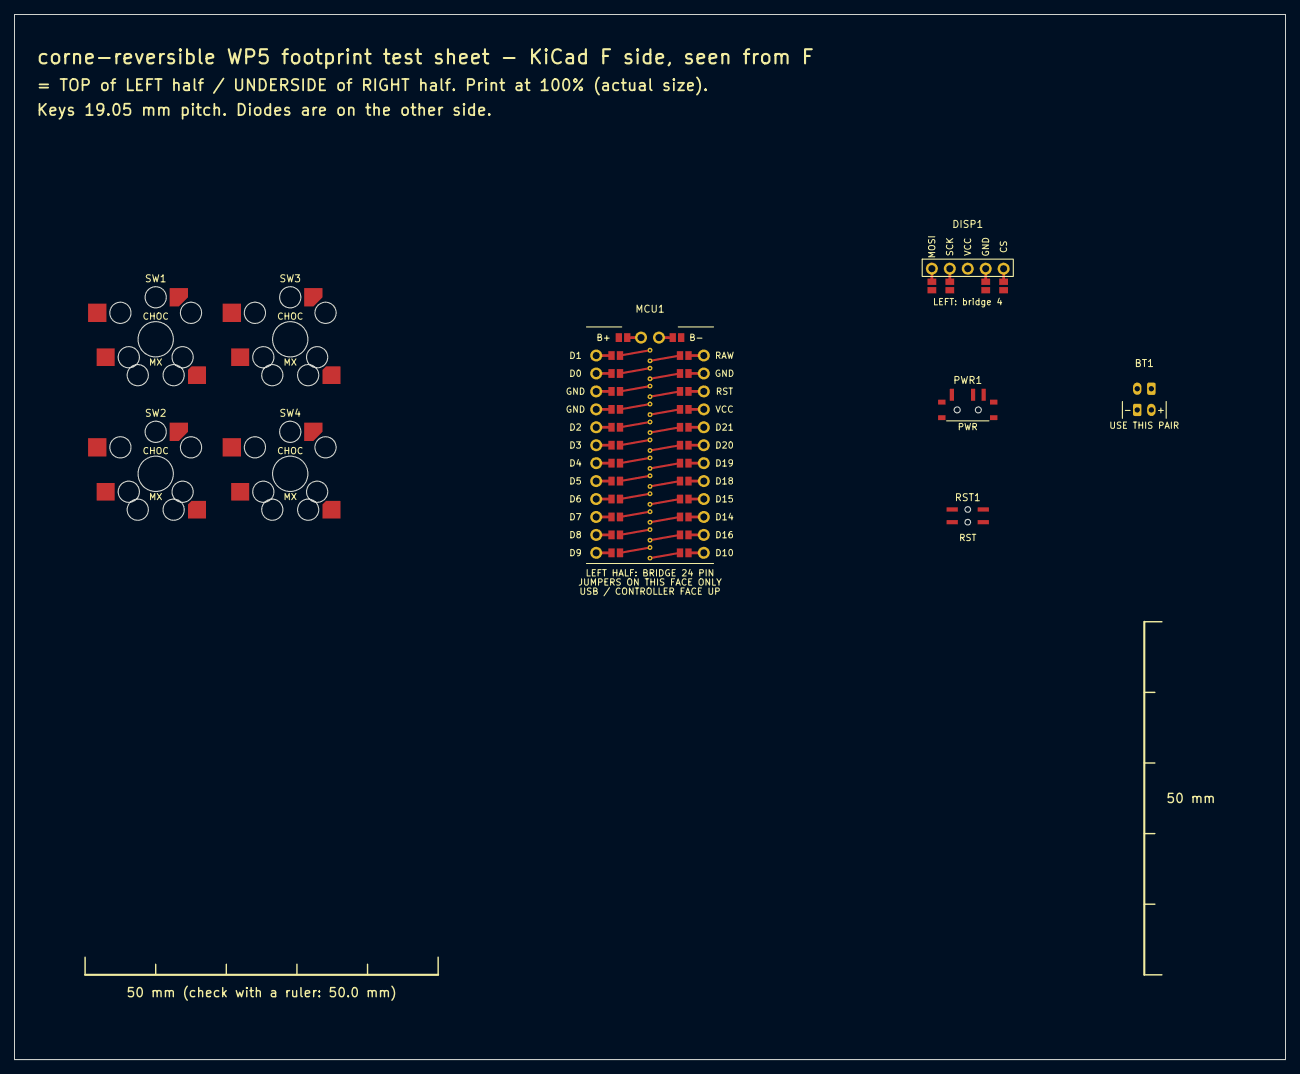
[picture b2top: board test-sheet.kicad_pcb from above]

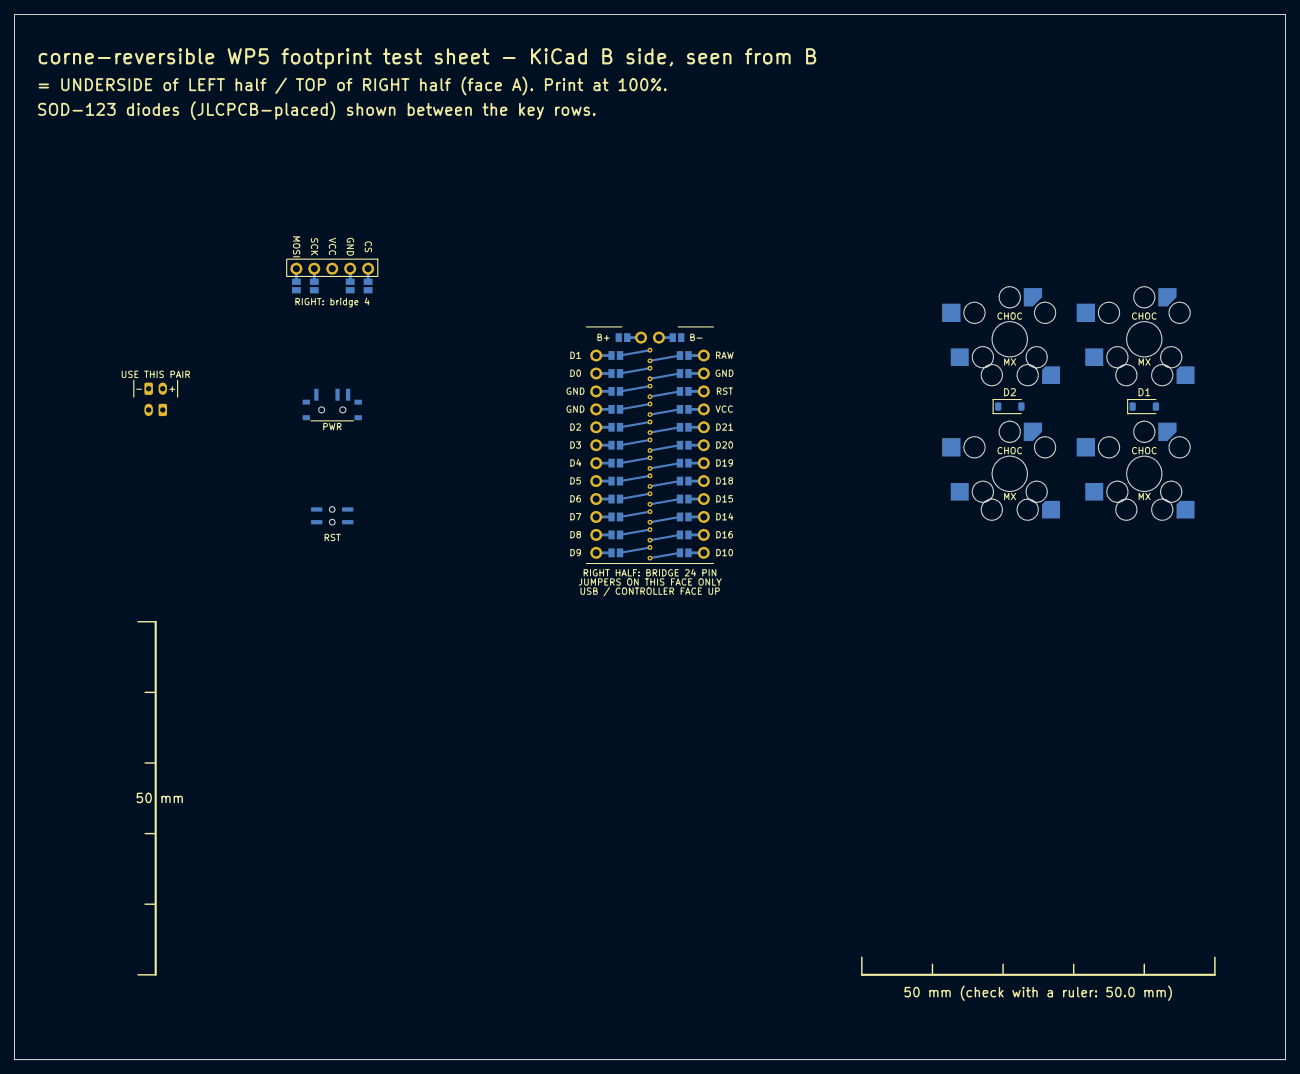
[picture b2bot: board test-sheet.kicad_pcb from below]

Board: 2 copper layers, 180.0 x 148.0 mm, 11 parts (2 on the bottom side), 10 nets, no tracks yet.

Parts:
BT1: JST_PH_S2B-PH-K_Reversible
D1, D2: D_SOD-123
DISP1: Display_niceview_Header_Reversible_Jumpers
MCU1: MCU_ProMicro_nRF52840_Reversible_Jumpers
PWR1: SW_SPDT_MSK12C02_Reversible
RST1: SW_Reset_TS-1186F_Side_Reversible
SW1, SW2, SW3, SW4: SW_MX_Choc_Hotswap_Reversible

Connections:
BAT_P: BT1.2, PWR1.1
COL0: SW1.1, SW2.1
COL1: SW3.1, SW4.1
GND: BT1.1, DISP1.GND, MCU1.GND, RST1.2
RAW: MCU1.RAW, PWR1.2
ROW1: D1.1, D2.1
RST: MCU1.RST, RST1.1
SW2-D: D1.2, SW2.2
SW4-D: D2.2, SW4.2
VCC: DISP1.VCC, MCU1.VCC

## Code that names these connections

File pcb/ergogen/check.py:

#!/usr/bin/env python3
"""Geometry and net checks for the generated board. Run after:
    npx ergogen@4.2.1 . -o output --clean --debug --svg
Usage: python3 check.py            (from pcb/ergogen)
Needs PyYAML only for output/points/points.yaml.
"""
import math, re, sys, yaml

PITCH = 19.05
TOL = 0.001
fails = []

def check(cond, msg):
    print(("PASS  " if cond else "FAIL  ") + msg)
    if not cond:
        fails.append(msg)

pts = yaml.safe_load(open("output/points/points.yaml"))
cols = {}
for name, p in pts.items():
    z, c, r = name.split("_")
    if z == "matrix":
        cols.setdefault(c, {})[r] = p
order = ["outer", "pinky", "ring", "middle", "index", "inner"]
rows = ["top", "home", "bottom"]

# 1. vertical spacing in each matrix column
for c in order:
    for a, b in zip(rows, rows[1:]):
        d = cols[c][a]["y"] - cols[c][b]["y"]
        dx = cols[c][a]["x"] - cols[c][b]["x"]
        check(abs(d - PITCH) < TOL and abs(dx) < TOL,
              f"column {c}: {a}->{b} dy={d:.4f} mm dx={dx:.4f}")
# 2. horizontal spacing between columns
for a, b in zip(order, order[1:]):
    d = cols[b]["home"]["x"] - cols[a]["home"]["x"]
    check(abs(d - PITCH) < TOL, f"columns {a}->{b}: dx={d:.4f} mm")
# 3. stagger relative to the middle column, in units of 19.05 mm (crkbd: 0.3 .3 .1 0 .1 .2 down)
exp = dict(zip(order, [0.3, 0.3, 0.1, 0.0, 0.1, 0.2]))
for c in order:
    down = (cols["middle"]["home"]["y"] - cols[c]["home"]["y"]) / PITCH + 0.0
    check(abs(down - (exp[c] - exp["middle"])) < 0.001,
          f"stagger {c}: {down:+.3f} u below middle, expected {exp[c]-exp['middle']:+.3f}")

# 4. PCB file: footprint list, diode offsets, nets
txt = open("output/pcbs/corne_reversible.kicad_pcb").read()
fps = re.split(r"\n  \(footprint ", txt)[1:]
info = []
for f in fps:
    m = re.match(r'"([^"]+)"', f)
    a = re.search(r"\(at ([-0-9.e]+) ([-0-9.e]+)(?: ([-0-9.e]+))?\)", f)
    info.append((m.group(1), float(a.group(1)), float(a.group(2)), float(a.group(3) or 0), f))
sw = [i for i in info if "SW_MX_Choc" in i[0]]
dd = [i for i in info if "D_SOD-123_Back" in i[0]]
check(len(sw) == 21 and len(dd) == 21, f"21 switches and 21 diodes (got {len(sw)}, {len(dd)})")
# each diode must be 9.525 mm from exactly one switch, below it in the key frame
ok = 0
for d in dd:
    best = None
    for s in sw:
        dist = math.hypot(d[1] - s[1], d[2] - s[2])
        if best is None or dist < best[0]:
            best = (dist, s)
    if abs(best[0] - PITCH / 2) < 0.01 and abs(d[3] - best[1][3]) < 0.01:
        ok += 1
check(ok == 21, f"every diode is 9.525 mm from its key with the key's rotation ({ok}/21)")
check(all('layer "B.Cu"' in d[4].split("\n")[1] for d in dd), "all diodes on B.Cu (face A, left-half underside)")
# nets: each diode anode net == its switch pad 2 net; cathode in ROWn
def pad_nets(f, num):
    return set(re.findall(r'\(pad "%s"[^\n]*\(net \d+ "([^"]+)"\)' % num, f))
def pad_nets2(f, num):
    return set(re.findall(r'\(pad "%s".*?\(net "?\d*"? ?"?([A-Za-z0-9_]+)"?\)' % num, f))
bad = 0
for d in dd:
    a = pad_nets(d[4], 2) or pad_nets2(d[4], 2)
    k = pad_nets(d[4], 1) or pad_nets2(d[4], 1)
    if not (len(a) == 1 and len(k) == 1 and list(k)[0].startswith("ROW") and list(a)[0].startswith("SW_")):
        bad += 1
check(bad == 0, f"diode anode on SW_* net, cathode on ROWn ({21-bad}/21)")
cn = set()
for s in sw:
    cn |= pad_nets(s[4], 1) or pad_nets2(s[4], 1)
check(cn == {"COL_D21", "COL_D20", "COL_D19", "COL_D18", "COL_D15", "COL_D14"}, f"switch pad 1 nets: {sorted(cn)}")
mcu = [i for i in info if "MCU_" in i[0]][0][4]
for pin, net in [("D4", "ROW0"), ("D5", "ROW1"), ("D6", "ROW2"), ("D7", "ROW3"), ("D21", "COL_D21"),
                 ("D20", "COL_D20"), ("D19", "COL_D19"), ("D18", "COL_D18"), ("D15", "COL_D15"),
                 ("D14", "COL_D14"), ("D1", "DISP_CS"), ("D2", "DISP_MOSI"), ("D3", "DISP_SCK")]:
    check(net in (pad_nets(mcu, pin) or pad_nets2(mcu, pin)), f"controller {pin} -> {net}")

# 5. mounting holes survive removal of the outer-column tab (break line x = outer + 9.525)
bx = cols["outer"]["home"]["x"] + PITCH / 2
holes = [i for i in info if "MountingHole" in i[0]]
check(len(holes) == 5, f"5 mounting holes (got {len(holes)})")
check(all(h[1] > bx + 2.0 for h in holes), "all mounting holes are right of the break line by > 2 mm")
for i in info:
    if any(k in i[0] for k in ("MountingHole", "Reset", "SPDT", "JST", "MCU_", "Display")):
        print(f"      {i[0].split(':')[1]:48s} KiCad x={i[1]:8.3f} y={i[2]:8.3f} rot={i[3]:g}")

print("\nRESULT:", "ALL PASS" if not fails else f"{len(fails)} FAILED")
sys.exit(1 if fails else 0)

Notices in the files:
parts and their libraries:
MX pads adapted from ceoloide/ergogen-footprints switch_mx (c) 2023 Marco Massarelli, MIT; see THIRD_PARTY.md.
